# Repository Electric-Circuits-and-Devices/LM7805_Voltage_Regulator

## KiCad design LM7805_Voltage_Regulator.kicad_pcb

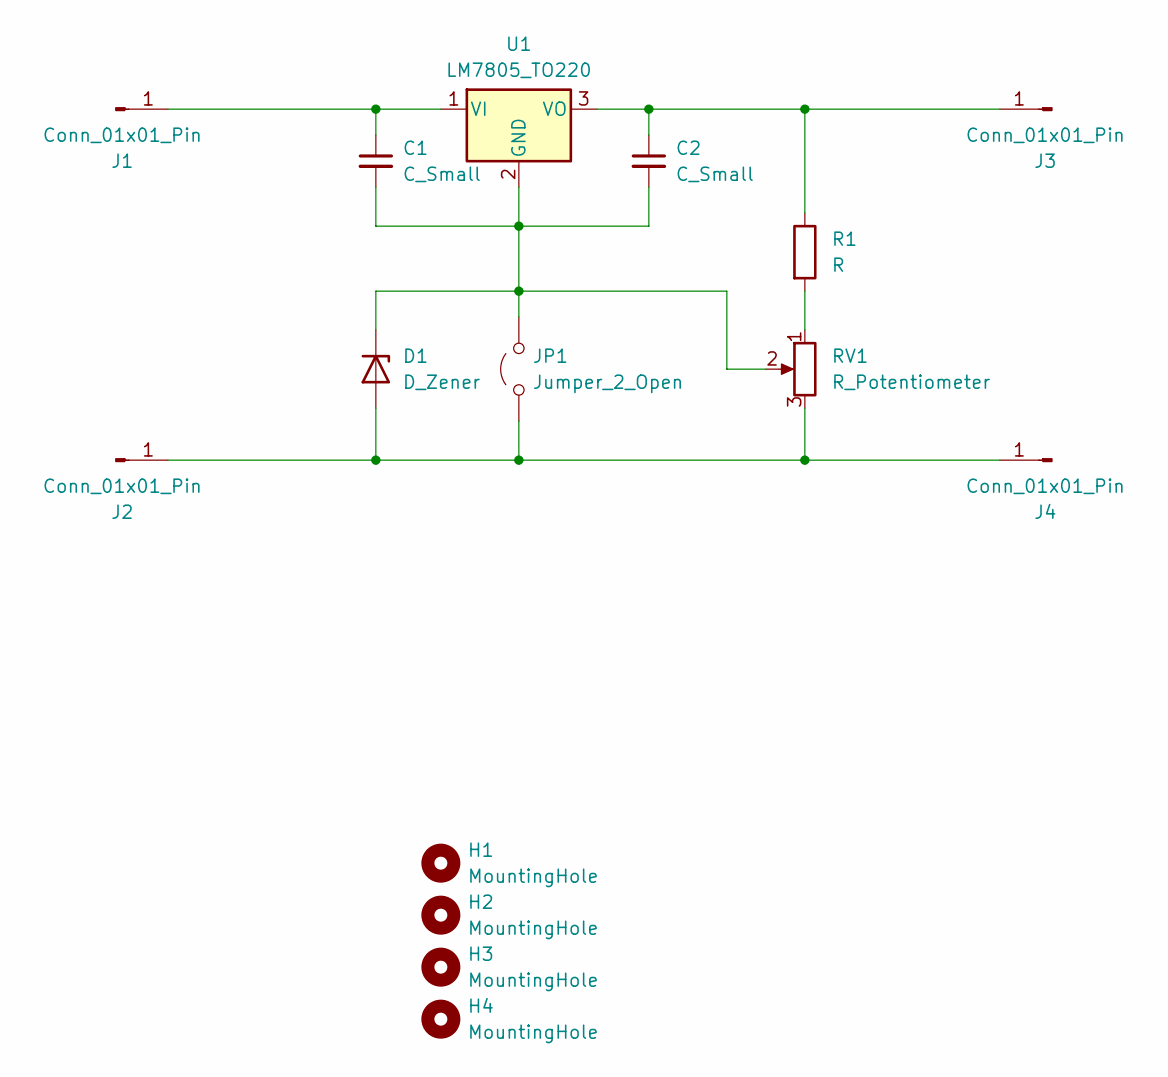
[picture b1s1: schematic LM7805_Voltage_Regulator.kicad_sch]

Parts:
C1, C2: C_Small; Capacitor-Plugin_Ceramic
D1: D_Zener; Zener-Diode-Plugin
H1, H2, H3, H4: MountingHole; MountingHole_3.2mm_M3_Pad
J1, J2, J3, J4: Conn_01x01_Pin; Banana_2mm
JP1: Jumper_2_Open; Jumper-Plugin
R1: R; Resistor-Plugin_0.5Watt
RV1: R_Potentiometer; Potentiometer_Alpha_RD901F-40-00D_Single_Vertical
U1: LM7805_TO220; TO-220-3_Vertical

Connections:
unnamed: D1.2 (A), J2.1, J4.1, JP1.1 (A), RV1.3
unnamed: C1.2, C2.2, D1.1 (K), JP1.2 (B), RV1.2, U1.2 (GND)
unnamed: C1.1, J1.1, U1.1 (VI)
unnamed: C2.1, J3.1, R1.1, U1.3 (VO)
unnamed: R1.2, RV1.1

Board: 2 copper layers, 15 parts (0 on the bottom side), 5 nets, no tracks yet.
